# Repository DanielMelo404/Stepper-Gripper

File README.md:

# Stepper-Gripper
Three fingers gripper with stepper motor

\section{Estado del arte - BCI:}
Una interfaz cerebro-computador es el conjunto de hardware y software que permite controlar dispositivos externos con señales cerebrales \cite{RAMADAN201726}.
El origen de este campo de investigación sucede en 1924 con Berger, el cual hace el primer grabado de señales por electro encefalografia (EEG), e identifica el patrón oscilatorio, con las ondas alpha (8-13Hz).

\section{Objetivos actuales del campo:}
\begin{itemize}
    \item Mejorar la calidad de vida de personas con heridas o enfermedades que afectan su sistema nervioso.
    \item Conectar a los seres humanos con la inteligencia artificial con el objetivo de que esta no nos deje atrás (Neuralink).
\end{itemize}

\section{Diseño}

\subsection{Requerimientos funcionales}

\begin{enumerate}
    \item Poder ser controlada remotamente
    \begin{enumerate}[label*=\arabic*.]
        \item Debe poder conectarse facilmente con plataformas que la puedan controlar \\
        \textbf{DP: Node-red}
        \item Poder conectarse a internet \\
        \textbf{DP: ESP32 WROOM}
    \end{enumerate}
    \item Poder sujetar objetos de distintos tamaños
    \textbf{DP: Motor acoplado a tornillo de potencia que mueve axialmente al hexagono de presion}
    \begin{enumerate}[label*=\arabic*.]
        \item Poder sostener una fuerza de 20N para sujetar al objeto.\\
        \textbf{DP: El motor, junto al sistema de transmisión de potencia}
        \item Se debe poder controlar la posición de la mano en su rango de movimiento con una precision suficiente como para ejercer presion sobre los objetos en su rango de sujeción.\\
        \textbf{DP: Motor stepper que con definición de 200 pasos por vuelta}
        \item Debe permitir mover el hexágono de presión linealmente sobre su recorrido.\\
        \textbf{DP: Eje de motor acoplado a tornillo de potencia cuyo carro esta sujeto al hexágono de presión}
        \begin{enumerate}[label*=\arabic*.]
            \item Debe sujetar al motor rotatoriamente sobre su eje, ejerciendo un apoyo para que el motor ejerza su torque.\\
            \textbf{DP: Hexagono acrilico en la base del motor} 
            \item Debe sujetar al motor y al sistema axialmente para que sobre el se delice el hexagono de presion y sin ejercer un troque en contra que trabe al motor.\\
            \textbf{DP: Rodamiento de sujeción axial que encaja en escalon en la parte superior final del eje}
            
        \end{enumerate}
        
    \end{enumerate}
    \item El diseño debe ser usable

    \textbf{DP: Interfaz de usuario de node-red (dashboard) e instrucciones de uso}
    \item El diseño debe ser repetible
    \textbf{DP: Repositorio con los archivos necesarios para reproducción y el informe del presente documento}
\end{enumerate}

\section{Análisis geométrico del mecanismo:}
El mecanismo esta conformado por 3 mecanismos de 4 barras. Los 3 se controlan por medio de dos eslabones y una pieza triangular al hexágono de presión, el cual tiene un recorrido de 3cm desde la posición superior hacia abajo. Esta conexión hace girar alrededor de su eje pinado al eslabón de entrada del mecanismo de 4 barras y por medio de esto logra su movimiento.

El eslabón biela (el que se sujeta en sus extremos a los eslabones que giran alrededor de sus conexiones pinadas) del mecanismo es la misma pata de agarre que sujeta al objeto. 
Al transladarse por el movimiento axial del hexagono presion, este eslabon dismuye su "altura" y se cierra sobre la posicion de agarre. De esta manera sujeta al objeto.

\subsection{Análisis relativo a la mano humana} 

Cutkosky, basándose en el trabajo de Napier, desarrollo una clasificacion de movimientos funcionalmente estudiando las poses de las manos de maquinistas en operaciones de manufactura. Segun Napier, la mano adquiere una posicion deacuerdo a lo que quiere lograr con el objeto. 

La poses de la mano se clasifican entonces posiciones de potencia y de precisión.

El mecanismo esta diseñado para permitir efectuar2 posiciones de precisión: trípode y esférica.

En lo seres humanos, el agarre trípode se utiliza para elevar objetos pequeños, pues es preciso. Además, los 3 dedos virtuales que componen el agarre permiten ejercer 3 puntos fuerza lateral y momentos, los cual lo hace ideal para sujetar el movimiento de un objeto en una trayectoria cuyas fuerzas están en dirección alrededor de los 360 grados del gripper. Un ejemplo en humanos de esta tarea es la escritura con lápiz o desenroscar un objeto sosteniendolo de 3 lugares con los dedos.

El agarre esferico tambien forma parte de los agarres de potencia. Por medio de tener un punto de apoyo directo en el marco de la maquina (o en el efector de mayor potencia como el braso en el caso humano), el movimiento realizado ahora puede involucrar mucha mayor fuerza, pues los dedos que rodean al objeto no estan haciendo empuje sino que estan haciendo fuerza en direccion radial para sujetar al objeto. De esta manera, se puede controlar el movimiento de un objeto con mayor potencia que con el agarre de tripode.

Ambos agarres también tienen la ventaja de permitir el agarre de objetos de distintas formas y tamaños, pues no solo se pueden sujetar objetos esfericos o cilindricos sino tambien objetos rectangulares o de forma irregular.

Solo con realizar un cambio en la posicion de sujecion en node-red, se puede ajustar el mecanismo para sujetar distintos objetos. 

%uso de iot: Recibir datos de utilizacion del producto para saber como esta. 
% Flexibilidad: Que por medio de unos cambios pueda pasar de ser una protesis a ser un brazo para proposito de investigacion.
% O en la plataforma.

\begin{figure}[h]
    \centering
    \includegraphics[width = 7cm]{image.png}
    \caption{Orquidea que inicialmente es plana pero cambia su forma cuando entra en contacto con el agua \cite{youtube2}}
    \label{fig:my_label}
\end{figure}

\section{}

\section{KPIs de la mano:}

\subsection{Máxima carga sujetada-probeta:}
Tiene el objetivo de medir la capacidad de sujetar de la mano. Depende totalmente de la geometría del eslabón final de agarre y de el coeficiente de fricción de este con la pieza. \\

El procedimiento para se muestra a continuación. Este KPI esta medido respecto a una sola forma de probeta, con el material definido por el usuario de la mano. En este caso se utilizo un recipiente de plástico HDPE circular en el que se deposita la carga en el centro. 

\begin{enumerate}
    \item Se posiciona la mano directamente encima de la posición de agarre. De manera que solo se requiera un movimiento vertical para que la pieza quede entre las pinzas.
    \item Se baja la mano hasta la posición de sujeción en donde este el diámetro de sujeción de la probeta.
    \item Se realiza el movimiento de la mano hasta llegar a un punto cercano al objeto. Apartir de este punto, para el apriete, se realiza el movimiento del gripper con pasos discretos (enviando uno por uno). Se aprieta hasta antes de que el motor se deslice un paso. Si ya se deslizo, debe repetirse el apriete.
    \item Se eleva la mano verticalmente a una aceleración de menos de $1 cm/s^2$ hasta una altura de por lo menos 10cm.
    
\end{enumerate}

Si el anterior procedimiento fue exitoso, se toma el peso de la probeta utilizada como el valor de este KPI. Este KPI no solo consta del peso cargado sino también de la probeta utilizada (peso y forma).

Por esto se deben informar ambas informaciones al informar sobre este KPI.

\subsection{}
Este KPI busca medir la usabilidad de la mano, es decir, la facilidad con la que se puede realizar la función que desempeña. A este punto, la mano esta enfocada a poder hacer uso del sistema de actuación de la mano para hacer el testeo y verificación de este.\\
De esta forma, se define este KPI por medio de medir la cantidad de tiempo que le toma a una persona mover por primera vez la mano.

Metodología para la obtención de este KPI:

\begin{enumerate}
    \item La persona lee las instrucciones de utilización de la mano por completo.
    \item Se le indica a la persona que haga que el gripper se mueva y se toma el tiempo desde que se le indica esto hasta que mueve por primera vez la mano.
\end{enumerate}

Este KPI asume que la persona que lo utilizara es el laboratorista Juan Camilo de la universidad o cualquier persona que halla estudiado el pregardo en ingenieria Mecanica o Mecatronica que ya halla cursado los prerequisitos de la materia APM o materias equivalentes.

Tambien se asume que la persona sabe como acceder a node-red y tambien al dashboard de este.

\begin{itemize}
    \item 
\end{itemize}

\section{Gemelo digital}

El gemelo digital permite la simulación del mecanismo de la mano en su rango de movimiento. El método de reproducción de su geometría fue la medición de las medidas con calibrador con una resolución de 0.02mm. Los ángulos fueron medidos con el goniómetro disponible en el laboratorio con las medidas con una resolución de 1 grado.

\begin{figure}[h]
    \centering
    \includegraphics[width = 7cm]{twin.png}
    \caption{Gemelo digital de la mano \cite{youtube2}}
    \label{fig:my_label}
\end{figure}

Así mismo el gemelo digital se verifico al imprimir las piezas en material PLA. Se encontraron desviaciones respecto a las dimensiones principales de \pm 1.3mm.

\begin{figure}[h]
    \centering
    \includegraphics[width = 7cm]{dash.png}
    \caption{Interfaz de usuario node-red \cite{youtube2}}
    \label{fig:my_label}
\end{figure}

El gemelo digital permite la simulacion del movimiento del mecanismo, lo cual sera util para previsualizar el movimiento del actuador una vez armado.

\section{IIoT}

\subsection{Conexion wifi}

El ESP32 utiliza las credenciales de la red, nombre de la red y contraseña de esta, para conectarse al inicio de su funcionamiento.
Las credenciales se ingresan directamente en el codigo del ESP32.

\begin{figure}[h]
    \centering
    \includegraphics[width = 7cm]{wifi.png}
    \caption{Conexion wifi}
    \label{fig:my_label}
\end{figure}

\subsection{Conexion MQTT}
El esquema de conexion se puede apreciar en el diagrama POA estatico. El ESP32 se conecta gracias a la libreria PubSubClient con el broker MQTT de hive. Alli crea un topico llamado StepperDMAOut y publica a este topico. Tambien se subsribe a un topico llamado stepperDMAin, a donde se envia la posicion del actuador.    

El servidor de Node-red, instaldo en alguna raspberry-pi o computador con conexion a internet, publica la informacion de posicion del actuador al topico stepperDMAin y se subscribe al topico stepperDMAout, del mismo borker Hive.

\begin{figure}[h]
    \centering
    \includegraphics[width = 7cm]{conect.png}
    \caption{Codigo para conexion con broker}
    \label{fig:my_label}
\end{figure}

\begin{figure}[h]
    \centering
    \includegraphics[width = 7cm]{node.png}
    \caption{Diagrama de node-red utilizado para la conexion con el broker}
    \label{fig:my_label}
\end{figure}

La informacion del usuario se captura por medio de los nodos slider y numeric, los cuales representan componentes de la interfaz de usuario en el dashboard de nodered.

\begin{figure}[h]
    \centering
    \includegraphics[width = 7cm]{node.png}
    \caption{Dashboard de node-red}
    \label{fig:my_label}
\end{figure}

La conexion con el broker MQTT se realiza por medio de los nodos receptor y publicador, los cuales utilizan la informacion de la direccion del broker, el nombre de los topicos y el puerto de este para realizar la conexion.

El dato enviado desde node red es la carga paga, la cual tiene el tipo de dato payload. Al llegar y salir del borker sale con tipo byte y en el ESP 32 se realiza su conversion a char y luego a int, para asi finalmentes ser utilizada como el numero de pasos que el motor dara desde su posicion de inicio.

La posicion de inicio corresponde a 0 pasos. Por esto la posicion del hexagono de presion debe comenzar desde el principio del recorrido del tornillo de potencia, en la parte superior.

\section{Electrónica y control del motor}

El circuito se compone del ESP32 y del driver del motor stepper. Tambien se utiliza un regulador de 5V para darle poder al ESP32, un capacitor de desacople para compensar cambios de corriente bruscos, y unos leds indicadores. Las borneras se utilizan para conectar con el motor y la bornera-conector para conectar la fuente de 12V.

El control del motor se realizo por medio de los pines step y dir. Una vez conectado el driver como se oberva en la figUra \cite{4988}, el pin step se debe conectar a algun GPIO del ESP32. Puede ser cualquiera pero se utilizo el GPIO 1. Cada vez que el motor da un paso, se envia un pulso por este pin. El pin dir se utiliza para controlar la direccion del motor. Tambien se puede conectar a cualquier GPIO pero se utilizo el GPIO 3.

\begin{figure}[h]
    \centering
    \includegraphics[width = 7cm]{a4988.png}
    \caption{Esquema de conexión para el driver}
    \label{4988}
\end{figure}

El circuito se manufacturo per medio de serigrafia en PCB y los archivs de Kicad se encuentran disponbiles en el repositorio "stepper gripper" de github. 

\begin{figure}[h]
    \centering
    \includegraphics[width = 7cm]{squema.png}
    \caption{Esquematico del circuito}
    \label{fig:my_label}
\end{figure}

\begin{figure}[h]
    \centering
    \includegraphics[width = 7cm]{circu.png}
    \caption{Circuito en PCB}
    \label{fig:my_label}
\end{figure}

\section{Control del movimiento del motor}

El control de movimiento se realizo por medio de la libreria accelstepper de Arduino. 

Se debe instanciar una interfaz de stepper indicando los pines de pasos y dirección. \cite{int}

\begin{figure}[h]
    \centering
    \includegraphics[width = 7cm]{acc.png}
    \caption{Instanciación de interfaz para motor}
    \label{int}
\end{figure}

El setup del stepper se muestra en la figura \cite{in2}. 
Estos parametros se utilzran cuando sele solicite al motor alcanzar una posicion. setAcceleration configura la aceleracion para el perfil trapezoidal que siguie el stepper entre posicion y posicion. La velocidad maxima durante recorrido trapezoidal tambien se cofigura con setMaxSpeed.

setSpeed se utiliza para configurar la velocidad a la que el motor se movera cuando lo haga a velocidad constante sin aceleracion o desaceleracion.

\begin{figure}[h]
    \centering
    \includegraphics[width = 7cm]{set.png}
    \caption{Establecimiento de parámetros iniciales para motor}
    \label{int2}
\end{figure}

El motor se controla en el ciclo loop por medio del codigo de la figura \ref{in3}. Requested position es la posicion solicitada y reachingPosition es la posición a la que se esta moviendo en ese momento en particular.
Si estas son distintas, se realiza el comando moveTo, el cual interrumpe el movimiento y hace que el motor inmediatamente comience a moverse hacia la posición señalada.

\begin{figure}[h]
    \centering
    \includegraphics[width = 7cm]{mot.png}
    \caption{Establecimiento de parámetros iniciales para motor}
    \label{in3}
\end{figure}

\section{Algoritmo de clasificación de señales}

\begin{figure}[h]
    \centering
    \includegraphics[width = 7cm]{mot.png}
    \caption{Establecimiento de parámetros iniciales para motor}
    \label{in3}
\end{figure}

\begin{figure}[h]
    \centering
    \includegraphics[width = 7cm]{mot.png}
    \caption{Establecimiento de parámetros iniciales para motor}
    \label{in3}
\end{figure}

El algoritmo 

\section{Conclusiones:} \label{sec:metodologia} %10min

\begin{itemize}
    \item La manufactura aditiva es poderosa cuando es utilizada en conjunto con un gemelo digital por medio de permitir la reproducción exacta de la pieza y de esta forma desacoplando el proceso de prototipado del objeto real.
    \item Node-red facilita la conexión con protocolo MQTT con borkers, por medio de la representación intuitiva con nodos y flujos del sistema de información
    \item Los motores steppers facilitan el control de movimiento por medio de no requerir un sistema de feedback para controlar su posición y al permitir un torque sostenido.
\end{itemize}

\begin{itemize}
   
\end{itemize}

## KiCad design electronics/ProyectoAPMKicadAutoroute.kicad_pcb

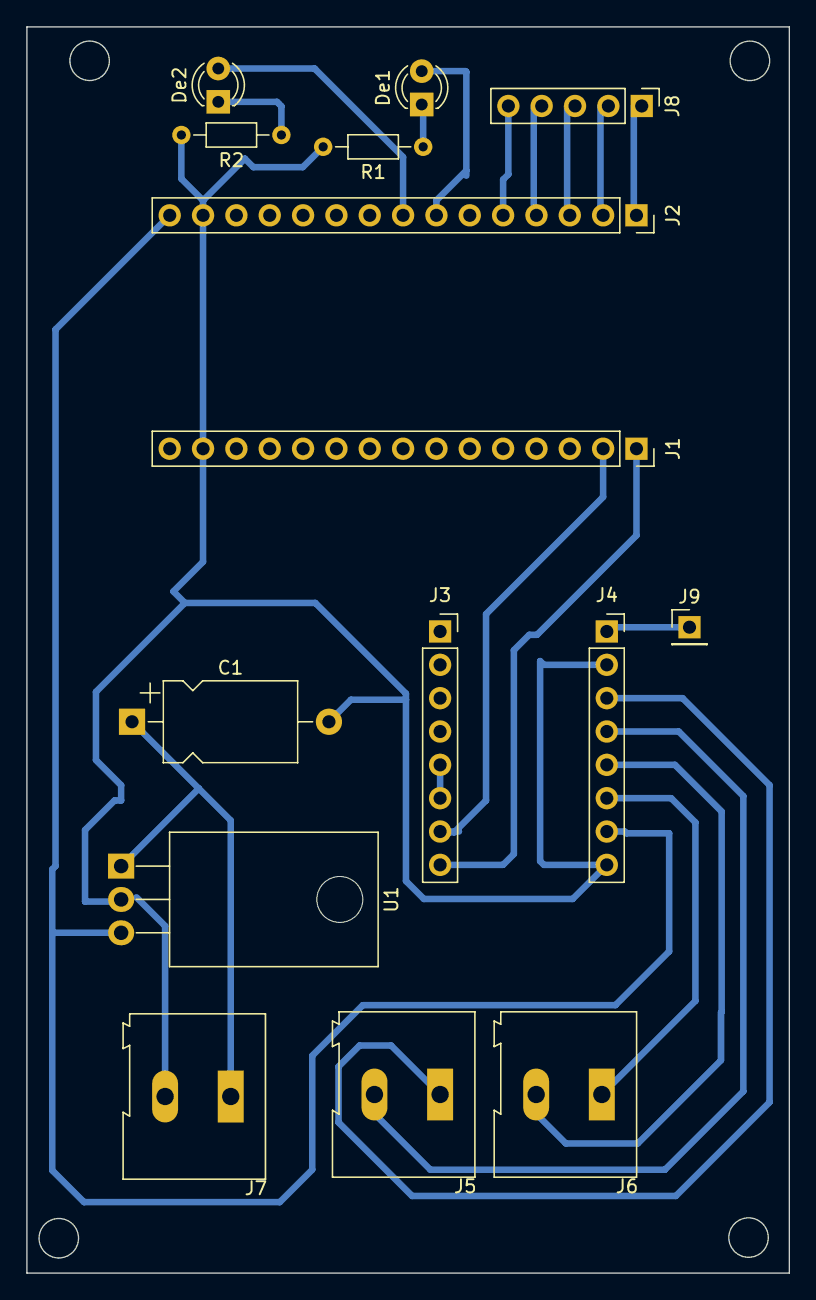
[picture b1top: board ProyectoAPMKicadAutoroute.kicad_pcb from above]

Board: 2 copper layers, 58.1 x 94.9 mm, 15 parts (0 on the bottom side), 20 nets.

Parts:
C1: 100u; CP_Axial_L10.0mm_D6.0mm_P15.00mm_Horizontal
De1, De2: LED; LED_D3.0mm_Clear
J1, J2: Conn_01x15_Socket; PinSocket_1x15_P2.54mm_Vertical
J3, J4: Conn_01x08_Socket; PinSocket_1x08_P2.54mm_Vertical
J5, J6, J7: Screw_Terminal_01x02; TerminalBlock_Altech_AK300-2_P5.00mm
J8: PicKit; PinHeader_1x05_P2.54mm_Vertical
J9: PicKit; PinHeader_1x01_P2.54mm_Vertical
R1, R2: 330; R_Axial_DIN0204_L3.6mm_D1.6mm_P7.62mm_Horizontal
U1: LM7805_TO220; TO-220-3_Horizontal_TabDown

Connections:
12V+: C1.1, J7.1, U1.1 (VI)
GND: C1.2, J1.14, J2.14, J4.2, J4.8, J7.2, R1.2, R2.2, U1.2 (GND)
unnamed: De1.2 (A), J2.7
unnamed: De1.1 (K), R1.1
unnamed: De2.2 (A), J2.8
unnamed: De2.1 (K), R2.1
unnamed: J2.1, J8.1
unnamed: J2.2, J8.2
unnamed: J2.3, J8.3
unnamed: J2.4, J8.4
unnamed: J2.5, J8.5
unnamed: J3.5, J3.6
unnamed: J4.1, J9.1
unnamed: J4.3, J5.1
unnamed: J4.4, J5.2
unnamed: J4.5, J6.2
unnamed: J4.6, J6.1
VDD: J2.15, J4.7, U1.3 (VO)
dir: J1.1, J3.8
step: J1.2, J3.7
